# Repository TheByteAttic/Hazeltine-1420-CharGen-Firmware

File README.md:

# Hazeltine 1420: character-generator adapters and firmware

Everything needed to keep the logic board of a Hazeltine 1420 video terminal (1979) alive when its
custom chips fail: plug-in replacements for the two proprietary character-generator ROMs, and copies
of the firmware for the CPU and its two program ROMs.

*The restored board. In the centre-left, the two green character-generator adapters sit in the
original U25/U26 sockets; below them the firmware ROMs U10 and U11, and the CPU U19.*

## Contents

| Directory | What it is |
|-----------|-----------|
| [`H1420-chargen-adapter/`](H1420-chargen-adapter/) | Two small boards that replace the National DM8678 and DM86S64 character generators with an EEPROM and four 74HCT chips: Gerbers, KiCad files, schematic, BOM, the fonts dumped from the original chips, the Arduino dumper, and the Python toolchain that designed and verified the boards |
| [`H1420-Bitsavers-firmware/`](H1420-Bitsavers-firmware/) | The terminal's firmware as preserved on bitsavers.org (images of U10, U11 and the 8049's internal ROM), the reference manual, and photos of the bitsavers unit |
| [`images/`](images/) | Photos of the boards and of the installation used in the READMEs |

## The chips this repository replaces

The 1420's logic board is built around an Intel 8049 microcontroller (U19) with two external program
ROMs, a 2716 EPROM (U10, addresses 0x000-0x7FF) and an 8316 mask ROM (U11, 0x800-0xFFF); the 8049's
own internal ROM is disabled (EA, pin 7, is tied high), so the CPU runs entirely from U10/U11. Display
timing comes from a National DP8350 CRT controller, and the characters themselves from two National
character generators, a DM8678 (control symbols and lower case) in U25 and a DM86S64 (capitals, digits,
punctuation) in U26.

Four of these parts are unobtainable today and three of them are custom to the terminal:

* **U10 and U11** can be rebuilt from the firmware images in `H1420-Bitsavers-firmware/`; both fit
  into ordinary 2716 EPROMs (pin 21 of both sockets is +5 V).
* **U19** can be any 8049, 8039 or 8749 since the internal ROM is not used; an 8749 programmed with the
  8049 image (also in the firmware folder) makes a self-contained spare.
* **U25 and U26** have no equivalent at all. The adapters in `H1420-chargen-adapter/` rebuild their
  function from current parts, using fonts dumped from the original chips.

*The two adapters in place: "UPPER 86S64" in U26, "LOWER 8678" in U25. The boards shown are revision A
with their jumpers bridged; revision B, in this repository, has that wiring in copper and no jumpers.*

## Quick start

1. Dead or dying character generator: read `H1420-chargen-adapter/README.md`. Dump your own chips
   first if they still work (`H1420-chargen-adapter/font/`); otherwise use the fonts there.
2. Dead firmware ROM or CPU: read `H1420-Bitsavers-firmware/README.md`.
3. Everything in here was built, installed and is running in the author's terminal.

## Credits

The firmware images, the reference manual and the photos of the bitsavers unit come from
[bitsavers.org](http://www.bitsavers.org/pdf/hazeltine/Hazeltine_1420/). The adapters, the font dumps
and the toolchain are by The Byte Attic B.V.

## Licence

MIT, see [`LICENSE`](LICENSE). The bitsavers material is redistributed as found there.

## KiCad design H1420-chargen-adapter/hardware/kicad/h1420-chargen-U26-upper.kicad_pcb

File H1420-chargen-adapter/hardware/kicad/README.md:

# KiCad boards

`h1420-chargen-U26-upper.kicad_pcb` and `h1420-chargen-U25-lower.kicad_pcb` are the same two layouts
as the Gerbers, as editable KiCad 8 board files. Footprints are embedded, so no library is needed;
there is no schematic project behind them (the design lives in `../../source/design.py`), so KiCad
will show the nets but cannot run a schematic/PCB comparison.

Open the board, press **B** to refill the ground zone, then plot if you want your own Gerbers.
Teardrops are plain copper polygons. The files were written by `../../source/export.py`; the
Gerbers in `../gerbers/` are the reference manufacturing data, not a KiCad plot.

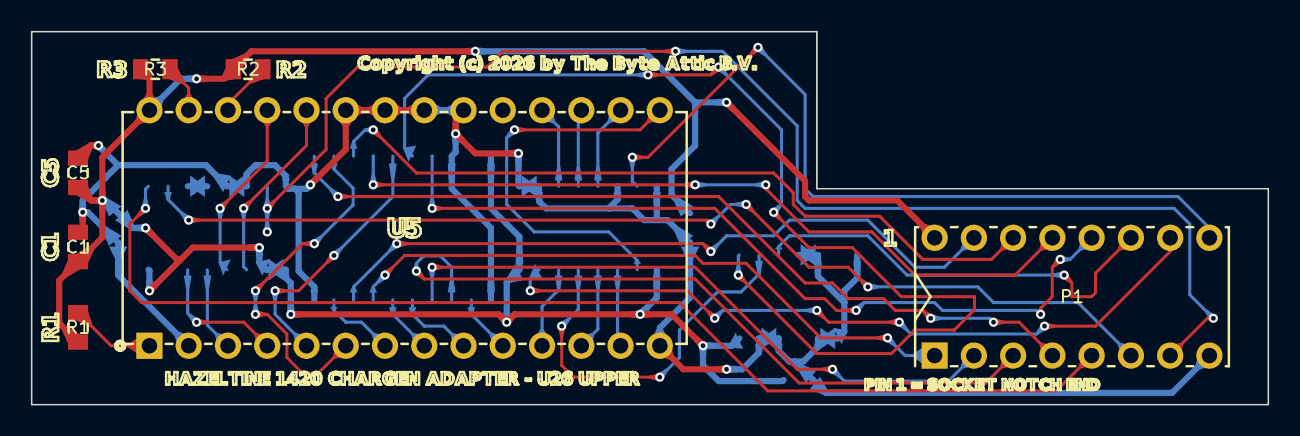
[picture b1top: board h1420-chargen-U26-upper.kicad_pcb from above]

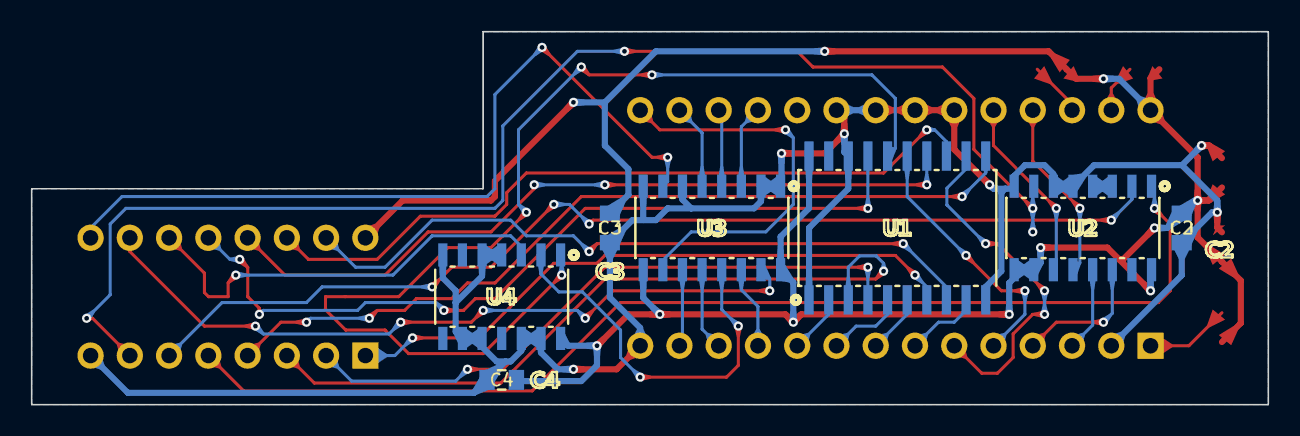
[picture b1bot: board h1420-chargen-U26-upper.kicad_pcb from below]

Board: 2 copper layers, 80.0 x 24.1 mm, 14 parts (7 on the bottom side), 38 nets.

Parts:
C1: 100nF; C1
C2: 100nF; C2
C3: 100nF; C3
C4: 100nF; C4
C5: 100nF; C5
P1: DIP-16 plug; P1
R1: 1k; R1
R2: 1k; R2
R3: 1k; R3
U1: 74HCT373D; U1
U2: 74HCT161D; U2
U3: 74HCT166D; U3
U4: 74HCT125D; U4
U5: AT28C64B-15PU; U5

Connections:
ADR0: P1.3, U1.3
ADR1: P1.2, U1.4
ADR2: P1.1, U1.7
ADR3: P1.15, U1.8
ADR4: P1.14, U1.13
ADR5: P1.13, U1.14
ALC: P1.4, U1.11
CC: P1.7, U2.7
D0: U3.14, U5.11
D1: U3.12, U5.12
D2: U3.11, U5.13
D3: U3.10, U5.15
D4: U3.5, U5.16
D5: U3.4, U5.17
D6: U3.3, U5.18
DCLK: P1.9, U3.7
GND: C1.2, C2.2, C3.2, C4.2, C5.2, P1.8, U1.1, U1.10, U1.18, U2.3, U2.4, U2.5, U2.6, U2.8, U3.1, U3.2, U3.6, U3.8, U4.4, U4.5, U4.7, U4.9, U4.10, U4.12, U4.13, U5.2, U5.14, U5.20, U5.21, U5.22, U5.23
LA0: U1.2, U5.10
LA1: U1.5, U5.9
LA2: U1.6, U5.8
LA3: U1.9, U5.7
LA4: U1.12, U5.6
LA5: U1.15, U5.5
LA7: U1.16, U4.1
LCLK: P1.6, U2.2
PIN11: P1.11, U4.3
PIN12: P1.12, U1.17
PU1: R1.2, U5.1
PU26: R2.2, U5.26
PU27: R3.2, U5.27
ROW0: U2.14, U5.4
ROW1: U2.13, U5.3
ROW2: U2.12, U5.25
ROW3: U2.11, U5.24
SER: U3.13, U4.2
VCC: C1.1, C2.1, C3.1, C4.1, C5.1, P1.16, R1.1, R2.1, R3.1, U1.20, U2.9, U2.10, U2.16, U3.9, U3.16, U4.14, U5.28
nCLR: P1.5, U2.1
nLD: P1.10, U3.15

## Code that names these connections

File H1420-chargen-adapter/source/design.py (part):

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net('CC',   ('P1', 7), ('U2', 7))                    # clock control -> counter CEP
net('DCLK', ('P1', 9), ('U3', 7))                    # dot clock -> shift register CP
net('nLD',  ('P1', 10), ('U3', 15))                  # load enable -> /PE
net('PIN11', ('P1', 11), ('U4', 3))                 # video out (was JP1 C-A)
net('PIN12', ('P1', 12), ('U1', 17))                 # pin 12 = A7, latched with the address
net('GND',  ('P1', 8), ('U1', 10), ('U2', 8), ('U3', 8), ('U4', 7), ('U5', 14),
    ('C1', 2), ('C2', 2), ('C3', 2), ('C4', 2), ('C5', 2),
    ('U1', 1), ('U1', 18),
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    return out

# ---------------------------------------------------------------- bus lanes (computed per variant)
BUS_NETS = ['ADR0', 'ADR1', 'ADR2', 'ADR3', 'ADR4', 'ADR5', 'ALC', 'PIN12', 'nCLR', 'LCLK', 'CC', 'DCLK', 'nLD']
LANE_PITCH = 0.762
LANE_X_END = 43.0
RAILS = {'U': [('VCC', 20.32), ('GND', 1.905)], 'L': [('VCC', mirror_y(20.32)), ('GND', mirror_y(1.905))]}
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
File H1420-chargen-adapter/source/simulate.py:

# Copyright (c) 2026 by The Byte Attic B.V.
"""Functional verification: build the adapter from the NETLIST (design.NETS, pin numbers) using
behavioural models of the 74x373 / 74x161 / EEPROM / 74x166 / 74x125, drive it with the
socket signals, and compare the serial video output cycle by cycle with a behavioural model
of the DM86S64 (datasheet 8-15..8-20) for both jumper positions.

Runs a randomised test: random font, random character streams, random line-clock / clear /
clock-control / address-latch / load / output-enable activity."""
import random
from design import NETS, check

pin2net = check()
def N(ref, pin):
    return pin2net.get((ref, pin))

# ---------------------------------------------------------------- reference model (DM86S64)
class DM86S64:
    def __init__(self, font):           # font[char][row] -> 7-bit int, bit0 = first dot out
        self.font = font
        self.latch = 0; self.counter = 0; self.sr = 0; self.out = 0
        self.prev_dot = 0; self.prev_line = 0
    def eval(self, addr, alc, nclr, lclk, cc, dclk, nld, noe):
        # address latch: transparent when alc high
        if alc: self.latch = addr & 63
        # counter: async clear, rising line clock when cc high
        if not nclr: self.counter = 0
        elif lclk and not self.prev_line and cc: self.counter = (self.counter + 1) & 15
        self.prev_line = lclk
        # shift register on rising dot clock
        if dclk and not self.prev_dot:
            if not nld:
                self.sr = self.font[self.latch][self.counter] & 0x7F   # 7 bits, bit0 = first out
            else:
                self.sr >>= 1                                          # zeros shift in
        self.prev_dot = dclk
        q = self.sr & 1
        return None if noe else q                                     # None = Hi-Z

class DM8678:
    """Independent model of the DM8678 from its logic diagram (datasheet p.7-117/118): seven address
    latches A1..A7 controlled by STROBE (low = hold), 1-of-64 decoder on A1..A6, 4-bit line counter
    with async /CLEAR, LINE RATE CLOCK and CLOCK CONTROL, 7-bit P.I.S.O. register with synchronous
    /LOAD on DOT RATE CLOCK, and a TRI-STATE output gated by the latched A7 (enabled when A7 = 0)."""
    def __init__(self, font):
        self.font = font
        self.lat = [0] * 7; self.cnt = 0; self.sr = [0] * 7
        self.p_dot = 0; self.p_line = 0
    def eval(self, a1_a6, a7, strobe, nclr, lclk, cc, dclk, nld):
        if strobe:                                    # fall-through while high
            self.lat = [(a1_a6 >> k) & 1 for k in range(6)] + [a7]
        if not nclr: self.cnt = 0
        elif lclk and not self.p_line and cc: self.cnt = (self.cnt + 1) & 15
        self.p_line = lclk
        if dclk and not self.p_dot:
            if not nld:
                code = sum(b << k for k, b in enumerate(self.lat[:6]))
                row = self.font[code][self.cnt] & 0x7F
                self.sr = [(row >> k) & 1 for k in range(7)]   # sr[0] = first dot out
            else:
                self.sr = self.sr[1:] + [0]
        self.p_dot = dclk
        return None if self.lat[6] else self.sr[0]

# ---------------------------------------------------------------- adapter built from the netlist
PIN373 = {'OE': 1, 'LE': 11, 'D': [3, 4, 7, 8, 13, 14, 17, 18], 'Q': [2, 5, 6, 9, 12, 15, 16, 19]}
PIN161 = {'MR': 1, 'CP': 2, 'P': [3, 4, 5, 6], 'CEP': 7, 'PE': 9, 'CET': 10, 'Q': [14, 13, 12, 11]}
PIN166 = {'SER': 1, 'IN': {2: 'A', 3: 'B', 4: 'C', 5: 'D', 10: 'E', 11: 'F', 12: 'G', 14: 'H'}, 'INH': 6, 'CLK': 7, 'CLR': 9, 'QH': 13, 'SHLD': 15}
PIN125 = {'OE': 1, 'A': 2, 'Y': 3}
PIN28C64 = {'A': [10, 9, 8, 7, 6, 5, 4, 3, 25, 24, 21, 23, 2], 'D': [11, 12, 13, 15, 16, 17, 18, 19], 'CE': 20, 'OE': 22, 'WE': 27}

class Adapter:
    def __init__(self, font, mode):
        self.image = {}
        for c in range(64):
            for r in range(16):
                self.image[r * 64 + c] = font[c][r] & 0x7F
        self.mode = mode                      # '8678' or '86S64' (jumper positions)
        self.q373 = [0] * 8; self.cnt = 0; self.sr = {k: 0 for k in 'ABCDEFGH'}
        self.prev_cp = 0; self.prev_clk = 0
    def eval(self, sock):
        """sock: dict socket-pin -> level (1..16), pins 11/12 per mode.  Returns output or None."""
        net = {}
        for p, v in sock.items():
            net[N('P1', p)] = v
        # jumper bridges
        if self.mode == '8678':      # JP1 C-A: VOUT->PIN11 ; JP2 C-A: nOE<-LA7
            oe_src = 'LA7'; out_pin = 11
        else:                        # JP1 C-B: VOUT->PIN12 ; JP2 C-B: nOE<-PIN11
            oe_src = 'PIN11'; out_pin = 12
        # 74x373: transparent when LE high, /OE low
        assert N('U1', PIN373['OE']) == 'GND'
        le = net[N('U1', PIN373['LE'])]
        d = [0 if N('U1', p) == 'GND' else net[N('U1', p)] for p in PIN373['D']]
        if le: self.q373 = d
        for k, p in enumerate(PIN373['Q']):
            if N('U1', p): net[N('U1', p)] = self.q373[k]
        # 74x161
        assert N('U2', PIN161['PE']) == 'VCC' and N('U2', PIN161['CET']) == 'VCC'
        mr = net[N('U2', PIN161['MR'])]; cp = net[N('U2', PIN161['CP'])]; cep = net[N('U2', PIN161['CEP'])]
        if not mr: self.cnt = 0
        elif cp and not self.prev_cp and cep: self.cnt = (self.cnt + 1) & 15
        self.prev_cp = cp
        for k, p in enumerate(PIN161['Q']):
            net[N('U2', p)] = (self.cnt >> k) & 1
        # EEPROM (CE, OE grounded, WE pulled up)
        assert N('U5', PIN28C64['CE']) == 'GND' and N('U5', PIN28C64['OE']) == 'GND' and N('U5', PIN28C64['WE']) == 'PU27'
        addr = 0
        for k, p in enumerate(PIN28C64['A']):
            n = N('U5', p)
            bit = 0 if n == 'GND' else net[n]
            addr |= bit << k
        data = self.image.get(addr, 0)
        for k, p in enumerate(PIN28C64['D']):
            n = N('U5', p)
            if n: net[n] = (data >> k) & 1
        # 74x166
        assert N('U3', PIN166['CLR']) == 'VCC' and N('U3', PIN166['INH']) == 'GND' and N('U3', PIN166['SER']) == 'GND'
        clk = net[N('U3', PIN166['CLK'])]; shld = net[N('U3', PIN166['SHLD'])]
        if clk and not self.prev_clk:
            if not shld:
                for p, name in PIN166['IN'].items():
                    n = N('U3', p)
                    self.sr[name] = 0 if n == 'GND' else net[n]
            else:
                order = 'HGFEDCBA'
                for i in range(7):
                    self.sr[order[i]] = self.sr[order[i + 1]]
                self.sr['A'] = 0    # SER = GND
        self.prev_clk = clk
        net[N('U3', PIN166['QH'])] = self.sr['H']
        # 74x125 gate 1
        assert N('U4', PIN125['A']) == 'SER' and N('U4', PIN125['Y']) == 'VOUT' and N('U4', PIN125['OE']) == 'nOE'
        noe = net[oe_src]
        y = None if noe else net['SER']
        # output pin check
        assert (out_pin == 11 and self.mode == '8678') or (out_pin == 12 and self.mode == '86S64')
        return y

# ---------------------------------------------------------------- random test
def run(seed, mode, cycles=6000):
    rnd = random.Random(seed)
    font = [[rnd.getrandbits(7) for r in range(16)] for c in range(64)]
    ref = DM86S64(font) if mode == '86S64' else DM8678(font); dut = Adapter(font, mode)
    addr = 0; alc = 1; nclr = 1; lclk = 0; cc = 1; nld = 1; noe = 0; a7 = 0
    dclk = 0; mism = 0; checked = 0
    for t in range(cycles):
        # slow signals change occasionally
        if rnd.random() < 0.15: addr = rnd.getrandbits(6)
        if rnd.random() < 0.10: alc ^= 1
        if rnd.random() < 0.03: nclr ^= 1
        if rnd.random() < 0.08: lclk ^= 1
        if rnd.random() < 0.05: cc ^= 1
        if rnd.random() < 0.20: nld ^= 1
        if rnd.random() < 0.10: noe ^= 1
        dclk ^= 1
        sock = {3: addr & 1, 2: (addr >> 1) & 1, 1: (addr >> 2) & 1, 15: (addr >> 3) & 1, 14: (addr >> 4) & 1, 13: (addr >> 5) & 1,
                4: alc, 5: nclr, 6: lclk, 7: cc, 9: dclk, 10: nld, 8: 0, 16: 1}
        if mode == '86S64':
            sock[11] = noe; sock[12] = 0          # pin 12 is our own output; value irrelevant
            exp = ref.eval(addr, alc, nclr, lclk, cc, dclk, nld, noe)
        else:
            # DM8678: A7 on pin 12 (latched with the address by STROBE = pin 4); pin 11 is our output
            sock[12] = noe; sock[11] = 0
            exp = ref.eval(addr, noe, alc, nclr, lclk, cc, dclk, nld)
        got = dut.eval(sock)
        checked += 1
        if got != exp:
            mism += 1
            if mism <= 5:
                print(f'  mismatch t={t}: expected {exp} got {got} (mode {mode})')
    return mism, checked

if __name__ == '__main__':
    total = 0
    for mode in ('86S64', '8678'):
        for seed in range(5):
            m, n = run(seed, mode)
            total += m
            print(f'mode {mode:6s} seed {seed}: {n} cycles, {m} mismatches')
    print('RESULT:', 'PASS' if total == 0 else f'FAIL ({total} mismatches)')

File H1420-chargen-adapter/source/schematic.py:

# Copyright (c) 2026 by The Byte Attic B.V.
"""Draw the schematic (net-label style) as a PDF with matplotlib."""
import matplotlib
matplotlib.use('Agg')
import matplotlib.pyplot as plt
from matplotlib.patches import Rectangle
from design import NETS, PARTS

PIN2NET = {}
for n, conns in NETS.items():
    for ref, pin in conns:
        PIN2NET[(ref, pin)] = n

PINNAMES = {
 'P1': {1: 'A2/A3', 2: 'A1/A2', 3: 'A0/A1', 4: 'ADDR LATCH', 5: '/CLEAR', 6: 'LINE CLOCK', 7: 'CLOCK CTRL', 8: 'GND',
        9: 'DOT CLOCK', 10: '/LOAD', 11: 'OUT|/OE', 12: 'A7|OUT', 13: 'A5/A6', 14: 'A4/A5', 15: 'A3/A4', 16: 'VCC'},
 'U1': {1: '/OE', 2: 'Q0', 3: 'D0', 4: 'D1', 5: 'Q1', 6: 'Q2', 7: 'D2', 8: 'D3', 9: 'Q3', 10: 'GND', 11: 'LE', 12: 'Q4', 13: 'D4', 14: 'D5',
        15: 'Q5', 16: 'Q6', 17: 'D6', 18: 'D7', 19: 'Q7', 20: 'VCC'},
 'U2': {1: '/MR', 2: 'CP', 3: 'D0', 4: 'D1', 5: 'D2', 6: 'D3', 7: 'CEP', 8: 'GND', 9: '/PE', 10: 'CET', 11: 'Q3', 12: 'Q2', 13: 'Q1', 14: 'Q0', 15: 'TC', 16: 'VCC'},
 'U3': {1: 'SER', 2: 'A', 3: 'B', 4: 'C', 5: 'D', 6: 'CLK INH', 7: 'CLK', 8: 'GND', 9: '/CLR', 10: 'E', 11: 'F', 12: 'G', 13: 'QH', 14: 'H', 15: 'SH//LD', 16: 'VCC'},
 'U4': {1: '/1OE', 2: '1A', 3: '1Y', 4: '/2OE', 5: '2A', 6: '2Y', 7: 'GND', 8: '3Y', 9: '3A', 10: '/3OE', 11: '4Y', 12: '4A', 13: '/4OE', 14: 'VCC'},
 'U5': {1: 'VPP/RDY/A15', 2: 'A12', 3: 'A7', 4: 'A6', 5: 'A5', 6: 'A4', 7: 'A3', 8: 'A2', 9: 'A1', 10: 'A0', 11: 'D0', 12: 'D1', 13: 'D2', 14: 'GND',
        15: 'D3', 16: 'D4', 17: 'D5', 18: 'D6', 19: 'D7', 20: '/CE', 21: 'A10', 22: '/OE', 23: 'A11', 24: 'A9', 25: 'A8', 26: 'NC/A13', 27: '/WE//PGM/A14', 28: 'VCC'},
}
TITLES = {'P1': 'P1  plug into DM8678 / DM86S64 socket (U25 / U26)', 'U1': 'U1  74HCT373  address latch', 'U2': 'U2  74HCT161  line counter',
          'U3': 'U3  74HCT166  dot shift register', 'U4': 'U4  74HCT125  tri-state output', 'U5': 'U5  AT28C64B  font EEPROM (DIP-28 socket)'}

def draw_ic(ax, ref, x, y, w, pins_left, pins_right, pitch=0.42):
    n = max(len(pins_left), len(pins_right))
    h = (n + 1) * pitch
    ax.add_patch(Rectangle((x, y - h), w, h, fill=False, lw=1.2))
    ax.text(x + w / 2, y + 0.15, TITLES.get(ref, ref), ha='center', va='bottom', fontsize=8.5, weight='bold')
    for k, p in enumerate(pins_left):
        py = y - (k + 1) * pitch
        ax.plot([x - 0.9, x], [py, py], 'k', lw=0.9)
        ax.text(x + 0.08, py, f'{p} {PINNAMES[ref].get(p, "")}', ha='left', va='center', fontsize=6.5)
        net = PIN2NET.get((ref, p), 'NC')
        ax.text(x - 1.0, py, net, ha='right', va='center', fontsize=7, color='#1a5276' if net not in ('GND', 'VCC') else '#7b241c')
    for k, p in enumerate(pins_right):
        py = y - (k + 1) * pitch
        ax.plot([x + w, x + w + 0.9], [py, py], 'k', lw=0.9)
        ax.text(x + w - 0.08, py, f'{PINNAMES[ref].get(p, "")} {p}', ha='right', va='center', fontsize=6.5)
        net = PIN2NET.get((ref, p), 'NC')
        ax.text(x + w + 1.0, py, net, ha='left', va='center', fontsize=7, color='#1a5276' if net not in ('GND', 'VCC') else '#7b241c')
    return h

def main(out='schematic.pdf'):
    fig = plt.figure(figsize=(16.5, 11.7))   # A3 landscape
    ax = fig.add_axes([0, 0, 1, 1]); ax.set_xlim(0, 42); ax.set_ylim(0, 29.7); ax.axis('off')
    ax.text(21, 28.9, 'Hazeltine 1420 character-generator adapter, rev B (replaces DM8678 / DM86S64 at U25 / U26)', ha='center', fontsize=14, weight='bold')
    ax.text(21, 28.3, 'net-label schematic: pins carrying the same label are connected. Two board variants (U26 upper / U25 lower) share this circuit.',
            ha='center', fontsize=9)
    # column 1: plug
    draw_ic(ax, 'P1', 2.6, 27.0, 5.6, [1, 2, 3, 4, 5, 6, 7, 8], [16, 15, 14, 13, 12, 11, 10, 9])
    ax.text(2.6, 22.7, 'pin 11 = video OUT, pin 12 = A7 / enable, active low', fontsize=6.5)
    ax.text(2.6, 22.3, '(same on both chips, measured)', fontsize=6.5)
    # column 2: latch + counter
    draw_ic(ax, 'U1', 11.8, 27.0, 3.2, [3, 4, 7, 8, 13, 14, 17, 18, 11, 1, 10], [2, 5, 6, 9, 12, 15, 16, 19, 20])
    draw_ic(ax, 'U2', 11.8, 20.6, 3.2, [2, 1, 7, 10, 9, 3, 4, 5, 6, 8], [14, 13, 12, 11, 15, 16])
    # column 3: EEPROM
    draw_ic(ax, 'U5', 20.4, 27.0, 3.6, [10, 9, 8, 7, 6, 5, 4, 3, 25, 24, 21, 23, 2, 20, 22, 14], [11, 12, 13, 15, 16, 17, 18, 19, 1, 26, 27, 28])
    # column 4: shift register + buffer
    draw_ic(ax, 'U3', 29.6, 27.0, 3.4, [14, 12, 11, 10, 5, 4, 3, 2, 1, 7, 15, 6, 9, 8], [13, 16])
    draw_ic(ax, 'U4', 29.6, 19.0, 3.4, [2, 1, 5, 4, 9, 10, 12, 13, 7], [3, 6, 8, 11, 14])
    # passives and jumpers text block
    txt = [
        'R1, R2, R3  1 kOhm 0805   VCC -> U5 pin 1, 26, 27  (nets PU1, PU26, PU27): keep /WE high on a 28C64,',
        '            set A13/A14/A15 high on a 27C256/27C512 (image block replicated, see build_eeprom.py)',
        'C1..C5      100 nF 0805 decoupling, one per IC (VCC-GND)',
        '',
        'Rev B: no jumpers.  Video out U4 pin 3 -> socket pin 11 (net PIN11); latched socket pin 12 (A7) -> U4 pin 1 /OE (net LA7).',
        '        (Rev A had solder jumpers JP1/JP2 for a DM86S64 pin assignment that turned out to be the same as the DM8678 one;',
        '         rev A boards are used with JP1 C-A and JP2 C-A bridged, which is exactly this wiring.)',
        '',
        'Output enable polarity: U4 = 74HCT125 -> output active when latched pin 12 is LOW, as measured on both original chips.',
        'If the font dump of a chip shows it outputs when pin 12 is HIGH, fit a 74HCT126 instead (same pinout, active-high enable).',
        '',
        'Logic family: 74HCT (TTL-compatible inputs, VIH = 2.0 V).  The terminal drives the socket with 74LS outputs (VOH >= 2.7 V),',
        'which plain 74HC (VIH = 3.5 V) would not reliably read.  Do not substitute 74HC for U1-U4.',
        '',
        'Timing: address -> latch (74HCT373, ~25 ns) -> EEPROM (150 ns) -> 74HC166 setup: ~190 ns < 280 ns spec of the',
        'original (t_S2).  Dot clock up to 25 MHz with 74HCT166; Hazeltine 1420 dot clock is below 20 MHz.',
        '',
        'Row address: the 74HC161 replaces the on-chip mod-16 line counter (CP = line clock, CEP = clock control,',
        '/MR = /clear).  Descender shifting of the original is baked into the EEPROM image row by row.',
        'Shift register: /LOAD -> SH//LD; DOT CLOCK -> CLK; EEPROM D0 (first dot) -> H ... D6 -> B; A and SER = 0,',
        'so the output goes low after the 7 dots exactly like the original.',
    ]
    for k, t in enumerate(txt):
        ax.text(1.0, 12.6 - k * 0.5, t, fontsize=7.8, family='monospace', va='top')
    ax.text(41.5, 0.4, 'Copyright (c) 2026 by The Byte Attic B.V.', ha='right', va='bottom', fontsize=8)
    fig.savefig(out)
    print('wrote', out)

if __name__ == '__main__':
    main()
